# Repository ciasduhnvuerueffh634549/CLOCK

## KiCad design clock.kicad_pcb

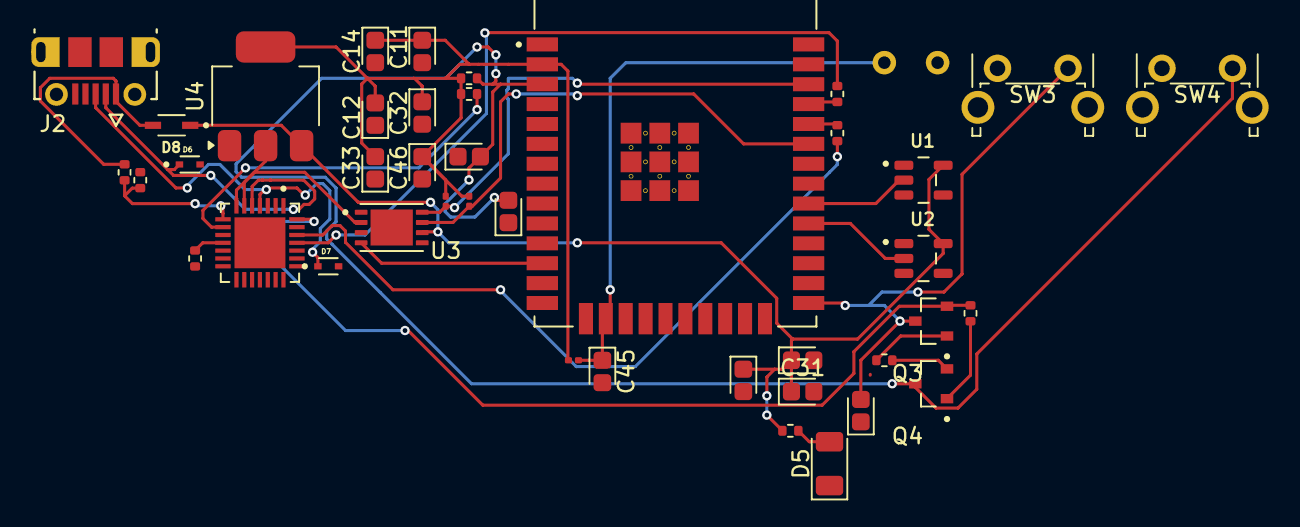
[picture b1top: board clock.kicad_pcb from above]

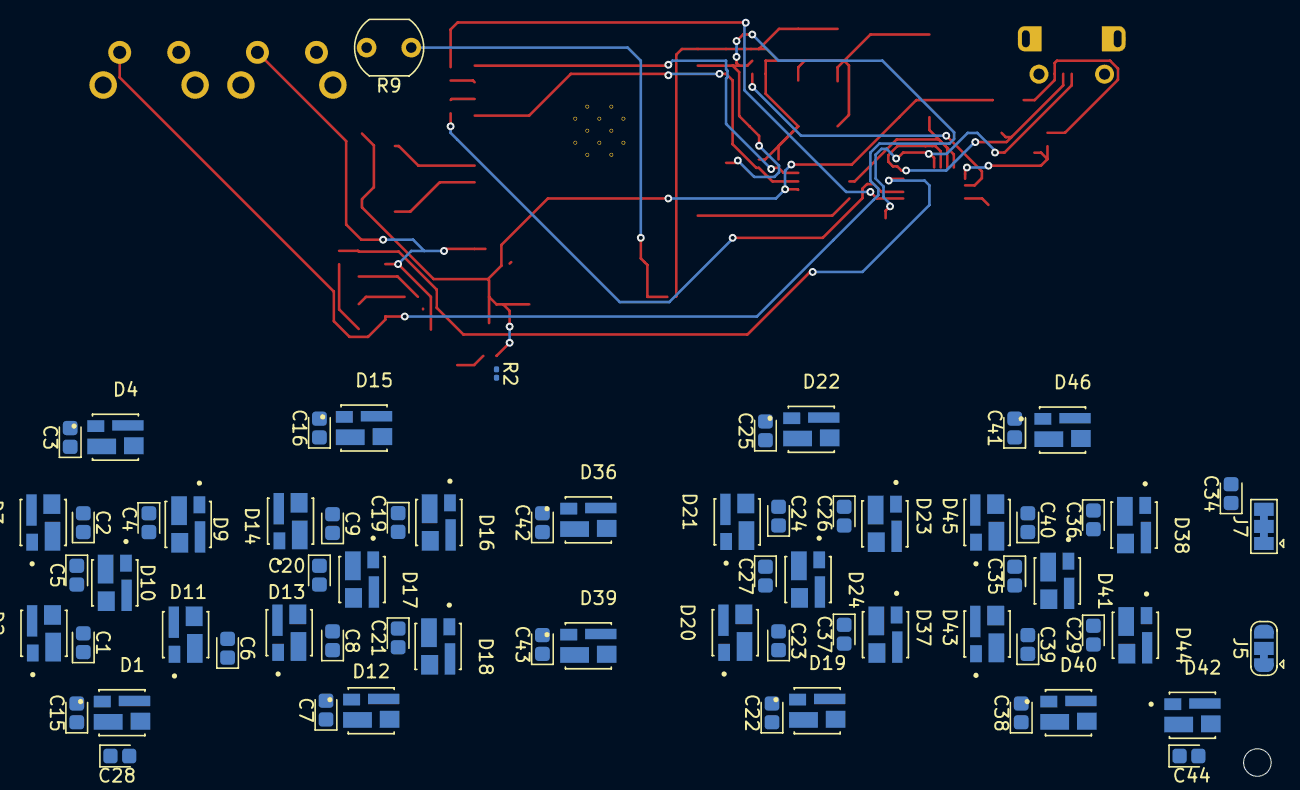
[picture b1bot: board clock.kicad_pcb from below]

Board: 2 copper layers, 113 parts (68 on the bottom side), 57 nets.

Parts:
C1, C2, C3, C4, C5, C6, C7, C8, C9, C15, C16, C19, C20, C21, C22, C23, C24, C25, C26, C27, C29, C30, C31, C34, C35, C36, C37, C38, C39, C40, C41, C42, C43, C44: 100nF; CP_EIA-1608-08_AVX-J
C10, C11, C14, C32: 22uF; CP_EIA-1608-08_AVX-J
C12, C13, C17, C18, C33, C45: 0,1uF; CP_EIA-1608-08_AVX-J
C28, C46: 1uF; CP_EIA-1608-08_AVX-J
D1, D2, D3, D4, D9, D10, D11, D12, D13, D14, D15, D16, D17, D18, D19, D20, D21, D22, D23, D24, D36, D37, D38, D39, D40, D41, D42, D43, D44, D45, D46: SK6812MINI-012; LED_SK6812MINI-012
D5: IR26-21C_L110_TR8; LED_1206_3216Metric
D6, D7: LESD5D5.0CT1G; TVS_LESD5D5.0CT1G
D8: BAT760-7; SOD2513X120N
H1, H2, H3, H4: GND; MountingHole_2.1mm
J2: 1050170001; MOLEX_1050170001
J5: Conn_01x03_Pin; SolderJumper-3_P1.3mm_Bridged12_RoundedPad1.0x1.5mm
J7: Conn_01x03_Pin; SolderJumper-3_P1.3mm_Bridged123_Pad1.0x1.5mm
Q3, Q4: SS8050-G; TRANS_SS8050-G
R2: 100m; R_0201_0603Metric
R4, R6, R7: 10k; R_0201_0603Metric
R9: LDR07; R_LDR_5.1x4.3mm_P3.4mm_Vertical
R11: 22.1K; R_0402_1005Metric
R12: 47.5K; R_0402_1005Metric
R13: R; R_0402_1005Metric
R14: 2K; R_0402_1005Metric
R15, R16, R19, R20: 10K; R_0402_1005Metric
R17: o; R_0402_1005Metric
R18: 0; R_0402_1005Metric
SW3, SW4: SW_Push; SW_Tactile_SPST_Angled_PTS645Vx31-2LFS
U1, U2: SN74LV1T34DBVR; SOT95P280X145-5N
U3: MAX31343ETAY_; SON65P300X400X80-9N
U4: AMS1117-3.3; SOT-223-3_TabPin2
U5: CP2102N-A02-GQFN28; QFN50P500X500X80-29N
U6: ESP32-WROOM-32; MODULE_ESP32-WROOM-32

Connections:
+3.3V: C11.1, C12.2, C14.1, C32.1, C33.2, C46.1, R4.1, R6.1, R7.1, R13.2, R16.1, U3.2 (VCC), U4.2 (VO), U5.6 (VDD), U5.7 (VREGIN), U6.2 (3V3)
+5V: C10.1, C30.1, C31.1, D8.C, R2.1, R14.1, U1.5 (VCC), U2.5 (VCC), U3.6 (VBAT), U4.3 (VI)
CLK_1HZ: U3.4 (SQW), U6.12 (IO27)
DTR: Q3.2, R19.1, U5.28 (DTR)
EN: C13.2, C17.2, Q4.3, R16.2, SW4.2, U6.3 (EN)
EXT_LEDS: C1.1, C2.1, C3.1, C4.1, C5.1, C6.1, C7.1, C8.1, C9.1, C15.1, C16.1, C19.1, C20.1, C21.1, C22.1, C23.1, C24.1, C25.1, C26.1, C27.1, C28.1, C29.1, C34.1, C35.1, C36.1, C37.1, C38.1, C39.1, C40.1, C41.1, C42.1, C43.1, C44.1, D1.2 (VDD), D2.2 (VDD), D3.2 (VDD), D4.2 (VDD), D9.2 (VDD), D10.2 (VDD), D11.2 (VDD), D12.2 (VDD), D13.2 (VDD), D14.2 (VDD), D15.2 (VDD), D16.2 (VDD), D17.2 (VDD), D18.2 (VDD), D19.2 (VDD), D20.2 (VDD), D21.2 (VDD), D22.2 (VDD), D23.2 (VDD), D24.2 (VDD), D36.2 (VDD), D37.2 (VDD), D38.2 (VDD), D39.2 (VDD), D40.2 (VDD), D41.2 (VDD), D42.2 (VDD), D42.3 (DOUT), D43.2 (VDD), D44.2 (VDD), D45.2 (VDD), D46.2 (VDD), J5.1, J5.3, J7.1, J7.3, R2.2
GND: C1.2, C2.2, C3.2, C4.2, C5.2, C6.2, C7.2, C8.2, C9.2, C10.2, C11.2, C12.1, C13.1, C14.2, C15.2, C16.2, C17.1, C18.1, C19.2, C20.2, C21.2, C22.2, C23.2, C24.2, C25.2, C26.2, C27.2, C28.2, C29.2, C30.2, C31.2, C32.2, C33.1, C34.2, C35.2, C36.2, C37.2, C38.2, C39.2, C40.2, C41.2, C42.2, C43.2, C44.2, C45.2, C46.2, D1.4 (GND), D2.4 (GND), D3.4 (GND), D4.4 (GND), D5.1 (K), D6.2, D7.2, D9.4 (GND), D10.4 (GND), D11.4 (GND), D12.4 (GND), D13.4 (GND), D14.4 (GND), D15.4 (GND), D16.4 (GND), D17.4 (GND), D18.4 (GND), D19.4 (GND), D20.4 (GND), D21.4 (GND), D22.4 (GND), D23.4 (GND), D24.4 (GND), D36.4 (GND), D37.4 (GND), D38.4 (GND), D39.4 (GND), D40.4 (GND), D41.4 (GND), D42.4 (GND), D43.4 (GND), D44.4 (GND), D45.4 (GND), D46.4 (GND), J2.4 (ID), J2.5 (GND), J2.SH1 (SHIELD1), J2.SH2 (SHIELD2), J2.SH3 (SHIELD3), J2.SH4 (SHIELD4), J2.SH5 (SHIELD5), J2.SH6 (SHIELD6), J5.2, J7.2, R9.2, R12.2, R15.2, SW3.1, SW4.1, U1.3 (GND), U2.3 (GND), U3.5 (GND), U3.9 (GND), U4.1 (GND), U5.3 (GND), U5.29 (GND), U6.1 (GND), U6.15 (GND), U6.38 (GND), U6.39_1 (GND), U6.39_2 (GND), U6.39_3 (GND), U6.39_4 (GND), U6.39_5 (GND), U6.39_6 (GND), U6.39_7 (GND), U6.39_8 (GND), U6.39_9 (GND), U6.39_10 (GND), U6.39_11 (GND), U6.39_12 (GND), U6.39_13 (GND), U6.39_14 (GND), U6.39_15 (GND), U6.39_16 (GND), U6.39_17 (GND), U6.39_18 (GND), U6.39_19 (GND), U6.39_20 (GND), U6.39_21 (GND)
I2C1_SCL: R6.2, U3.8 (SCL), U6.36 (IO22)
I2C1_SDA: R7.2, U3.7 (SDA), U6.33 (IO21)
IO0: C18.2, Q3.3, SW3.2, U6.25 (IO0)
LE30_DIN: D36.3 (DOUT), D39.1 (DIN)
LED0_BUF: U1.2 (A), U6.30 (IO18)
LED0_DIN: D1.1 (DIN), U1.4 (Y)
LED1_DIN: D1.3 (DOUT), D2.1 (DIN)
LED2_DIN: D2.3 (DOUT), D3.1 (DIN)
LED3_DIN: D3.3 (DOUT), D4.1 (DIN)
LED4_DIN: D4.3 (DOUT), D9.1 (DIN)
LED5_DIN: D9.3 (DOUT), D10.1 (DIN)
LED6_DIN: D10.3 (DOUT), D11.1 (DIN)
LED7_DIN: D11.3 (DOUT), D12.1 (DIN)
LED8_DIN: D12.3 (DOUT), D13.1 (DIN)
LED9_DIN: D13.3 (DOUT), D14.1 (DIN)
LED10_DIN: D14.3 (DOUT), D15.1 (DIN)
LED11_DIN: D15.3 (DOUT), D16.1 (DIN)
LED12_DIN: D16.3 (DOUT), D17.1 (DIN)
LED13_DIN: D17.3 (DOUT), D18.1 (DIN)
LED14_DIN: D18.3 (DOUT), D19.1 (DIN)
LED15_DIN: D19.3 (DOUT), D20.1 (DIN)
LED16_DIN: D20.3 (DOUT), D21.1 (DIN)
LED17_DIN: D21.3 (DOUT), D22.1 (DIN)
LED18_DIN: D22.3 (DOUT), D23.1 (DIN)
LED19_DIN: D23.3 (DOUT), D24.1 (DIN)
LED20_DIN: D24.3 (DOUT), D37.1 (DIN), U2.4 (Y)
LED21_DIN: D37.3 (DOUT), D40.1 (DIN)
LED22_DIN: D40.3 (DOUT), D43.1 (DIN)
LED23_DIN: D43.3 (DOUT), D45.1 (DIN)
LED24_DIN: D45.3 (DOUT), D46.1 (DIN)
LED25_DIN: D38.1 (DIN), D46.3 (DOUT)
LED26_DIN: D38.3 (DOUT), D41.1 (DIN)
LED27_DIN: D41.3 (DOUT), D44.1 (DIN)
LED29_BUF: U2.2 (A), U6.29 (IO5)
LED31_DIN: D39.3 (DOUT), D42.1 (DIN)
LIGHT_DECT: C45.1, R4.2, R9.1, U6.16 (IO13)
unnamed: D5.2 (A), R14.2
unnamed: Q3.1, R20.2
unnamed: Q4.1, R19.2
unnamed: R11.1, R12.1, U5.8 (VBUS)
unnamed: R13.1, U5.9 (~RST)
unnamed: R15.1, U5.11 (~SUSPEND)
RTS: Q4.2, R20.1, U5.24 (RTS)
RXD: R17.2, U5.25 (RXD)
RXD0: R18.1, U6.34 (RXD0)
TXD: R18.2, U5.26 (TXD)
TXD0: R17.1, U6.35 (TXD0)
USB_DN: D6.1, J2.2 (D-), U5.5 (D-)
USB_DP: D7.1, J2.3 (D+), U5.4 (D+)
VBUS: D8.A, J2.1 (VBUS), R11.2
